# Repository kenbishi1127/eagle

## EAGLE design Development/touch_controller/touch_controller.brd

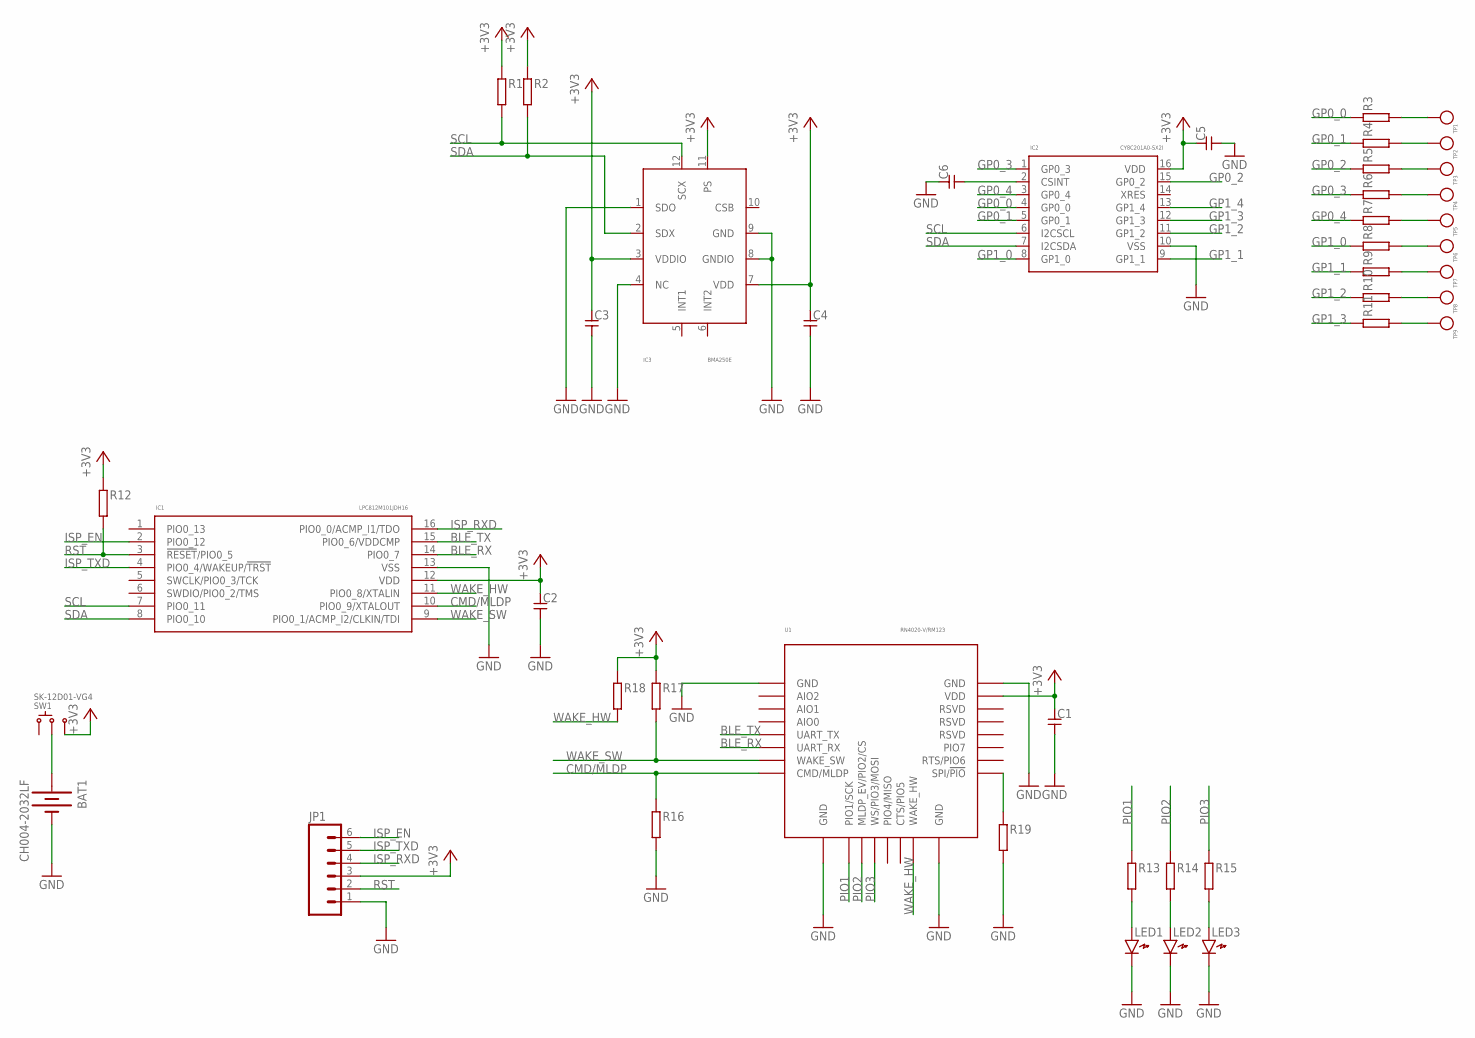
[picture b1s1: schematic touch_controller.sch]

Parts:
BAT1: CH004-2032LF
C1, C2, C3, C4, C5, C6: CAPACITOR1608_REDUCED; SMD1608_REDUCED
IC1: LPC812M101JDH16; TSSOP16
IC2: CY8C201A0-SX2I; SOIC-16
IC3: BMA250E; LGA-12
JP1: M06NOSILK; 1X06-NOSILK
LED1, LED2, LED3: LED1608_REDUCED
R1, R2, R3, R4, R5, R6, R7, R8, R9, R10, R11, R12, R13, R14, R15, R16, R17, R18, R19: RESISTOR1608_REDUCED; SMD1608_REDUCED
SW1: SK-12D01-VG4
TP1, TP2, TP3, TP4, TP5, TP6, TP7, TP8, TP9: HT-0720-10
U1: RN4020-V/RM123; RN4020

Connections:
+3V3: C1.1, C2.1, C3.1, C4.1, C5.1, IC1.12 (VDD), IC2.16 (VDD), IC3.3 (VDDIO), IC3.7 (VDD), IC3.11 (PS), JP1.3, R1.1, R2.1, R12.1, R17.1, R18.1, SW1.3, U1.23 (VDD)
BLE_RX: IC1.14 (PIO0_7), U1.6 (UART_RX)
BLE_TX: IC1.15 (PIO0_6/VDDCMP), U1.5 (UART_TX)
CMD/MLDP: IC1.10 (PIO0_9/XTALOUT), R16.1, U1.8 (CMD/MLDP)
GND: BAT1.-, C1.2, C2.2, C3.2, C4.2, C5.2, C6.1, IC1.13 (VSS), IC2.10 (VSS), IC3.1 (SDO), IC3.4 (NC), IC3.8 (GNDIO), IC3.9 (GND), JP1.1, LED1.K, LED2.K, LED3.K, R16.2, R19.2, U1.1 (GND), U1.9 (GND), U1.16 (GND), U1.24 (GND)
GP0_0: IC2.4 (GP0_0), R3.1
GP0_1: IC2.5 (GP0_1), R4.1
GP0_2: IC2.15 (GP0_2), R5.1
GP0_3: IC2.1 (GP0_3), R6.1
GP0_4: IC2.3 (GP0_4), R7.1
GP1_0: IC2.8 (GP1_0), R8.1
GP1_1: IC2.9 (GP1_1), R9.1
GP1_2: IC2.11 (GP1_2), R10.1
GP1_3: IC2.12 (GP1_3), R11.1
GP1_4: IC2.13 (GP1_4)
ISP_EN: IC1.2 (PIO0_12), JP1.6
ISP_RXD: IC1.16 (PIO0_0/ACMP_I1/TDO), JP1.4
ISP_TXD: IC1.4 (PIO0_4/WAKEUP/!TRST), JP1.5
unnamed: BAT1.+, SW1.2
unnamed: C6.2, IC2.2 (CSINT)
unnamed: R3.2, TP1.P$1
unnamed: R4.2, TP2.P$1
unnamed: R5.2, TP3.P$1
unnamed: R6.2, TP4.P$1
unnamed: R7.2, TP5.P$1
unnamed: R8.2, TP6.P$1
unnamed: R9.2, TP7.P$1
unnamed: R10.2, TP8.P$1
unnamed: R11.2, TP9.P$1
unnamed: R19.1, U1.17 (SPI/!PIO)
unnamed: LED1.A, R13.2
unnamed: LED2.A, R14.2
unnamed: LED3.A, R15.2
PIO1: R13.1, U1.10 (PIO1/SCK)
PIO2: R14.1, U1.11 (MLDP_EV/PIO2/CS)
PIO3: R15.1, U1.12 (WS/PIO3/MOSI)
RST: IC1.3 (!RESET!/PIO0_5), JP1.2, R12.2
SCL: IC1.7 (PIO0_11), IC2.6 (I2CSCL), IC3.12 (SCX), R1.2
SDA: IC1.8 (PIO0_10), IC2.7 (I2CSDA), IC3.2 (SDX), R2.2
WAKE_HW: IC1.11 (PIO0_8/XTALIN), R18.2, U1.15 (WAKE_HW)
WAKE_SW: IC1.9 (PIO0_1/ACMP_I2/CLKIN/TDI), R17.2, U1.7 (WAKE_SW)

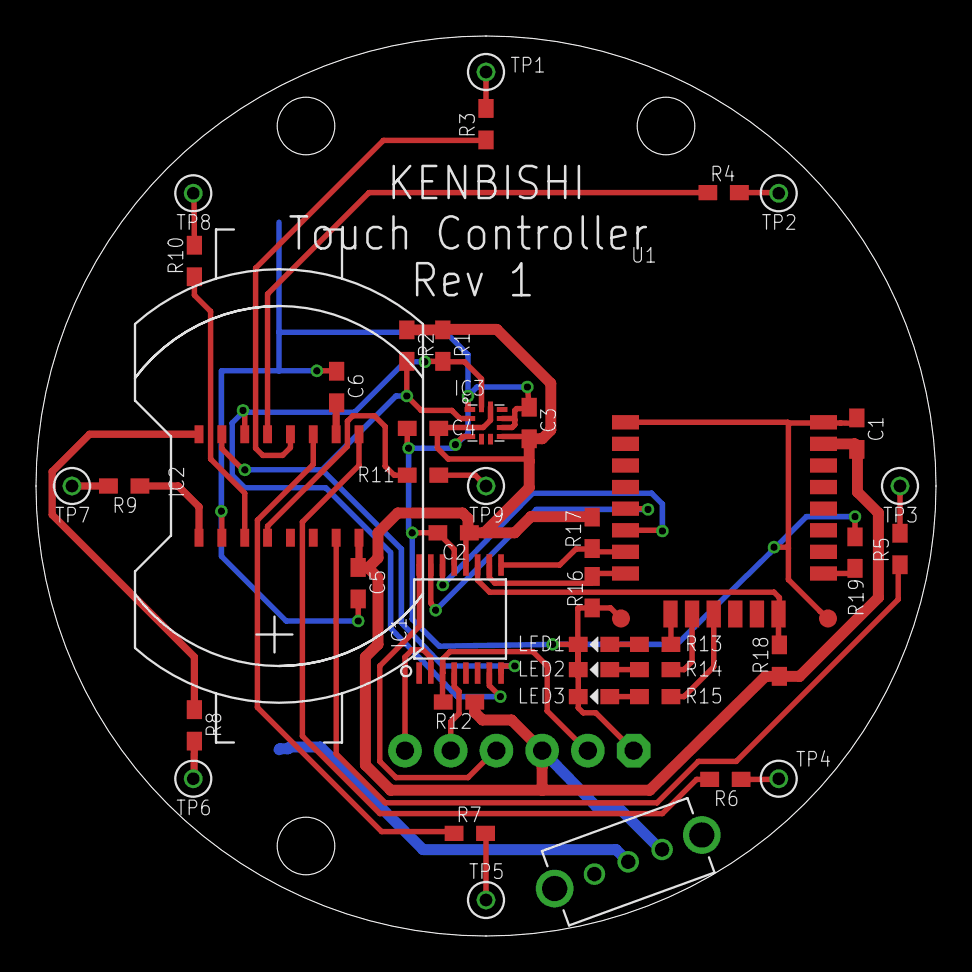
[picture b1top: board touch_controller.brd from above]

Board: 2 copper layers, 50.0 x 50.0 mm, 44 parts (1 on the bottom side), 40 nets.

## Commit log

2017-08-11 設計開始
2017-08-12 development フォルダ作成
2017-08-12 ライブラリ追加
2017-08-13 add library
2017-08-13 edit gitignore
2017-08-14 add cam file
2017-08-14 touch controller rev1
2017-08-14 edit library
2017-08-14 sphere robo設計開始
2017-08-16 add brd file
2017-08-16 test
2017-08-17 sphere_robo設計開始
